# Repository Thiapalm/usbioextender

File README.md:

# USB to IO Extender Board

<p align=center>

</p>

This is a hobby development board conceived for usage in my home lab. The board can be used as USB to serial adapter with no need to install any driver on the PC. It can be used as USB to I2C adapter and also USB to GPIO port extender. For the two later options, some code development may be necessary.  

The board has 4 extra GPIO ports that can be used as LED indicators (if the back jumpers are soldered). The board power is provided by the USB connector, and it can be used in 5V or 3V3 modes for serial, I2C and GPIO pins. 

## License and certification

This is an open source hardware project licensed under CERN-OHL-P. More details on [LICENSE.md](./LICENSE.md).  

This project is certified by OSHW: [Certification BR000019](https://certification.oshwa.org/br000019.html)

## Project

The PCB project was developed in Kicad 9, all necessary project files are available in this repository and can be used freely, according to License.

## Board specifications

The board is based on the [**MCP2221**](https://www.microchip.com/en-us/product/MCP2221), and [**MCP23017**](https://www.microchip.com/en-us/product/MCP23017) from Microchip.  
Board features commonly used in Embedded Systems:
- USB-C connector
- I²C serial communication
- UART serial communication
- LED indicators (UART-TX, UART-RX, I²C, USB-Config and board power ON) or 4 extra GPIOs
- 16 GPIOs (5V or 3V3)
- Board power selector (5V / 3V3)
- The GPIO pins are breadboard compatible

## Board View 

## Version Revision

V1 - Not Published  
   - Added MCP23017 GPIOs on the header  
   - Added Jumper selector on LEDs  
   - Added Output voltage selection  
   - Added MCP2221 serial on Header  
   - Added MCP2221 I2C on Header   

V2 - Current Version
   - Changed USB connector to USB-C

## Firmware

There is no specific firmware for this board, but i have a driver developed in RUST for MCP23017 for use in embedded environments, see it in [crates.io](https://crates.io/crates/mcp23017-tp).

Also, you can use the IOExtender Control Center which is a software that can be used to control the I²C communication via Windows/Linux/Mac machines [iocc software](https://github.com/Thiapalm/iocc).

## Contribution

Unless you explicitly state otherwise, any contribution intentionally submitted for inclusion in the work by you, as defined in the CERN-OHL-P license, shall be licensed as above, without any additional terms or conditions.

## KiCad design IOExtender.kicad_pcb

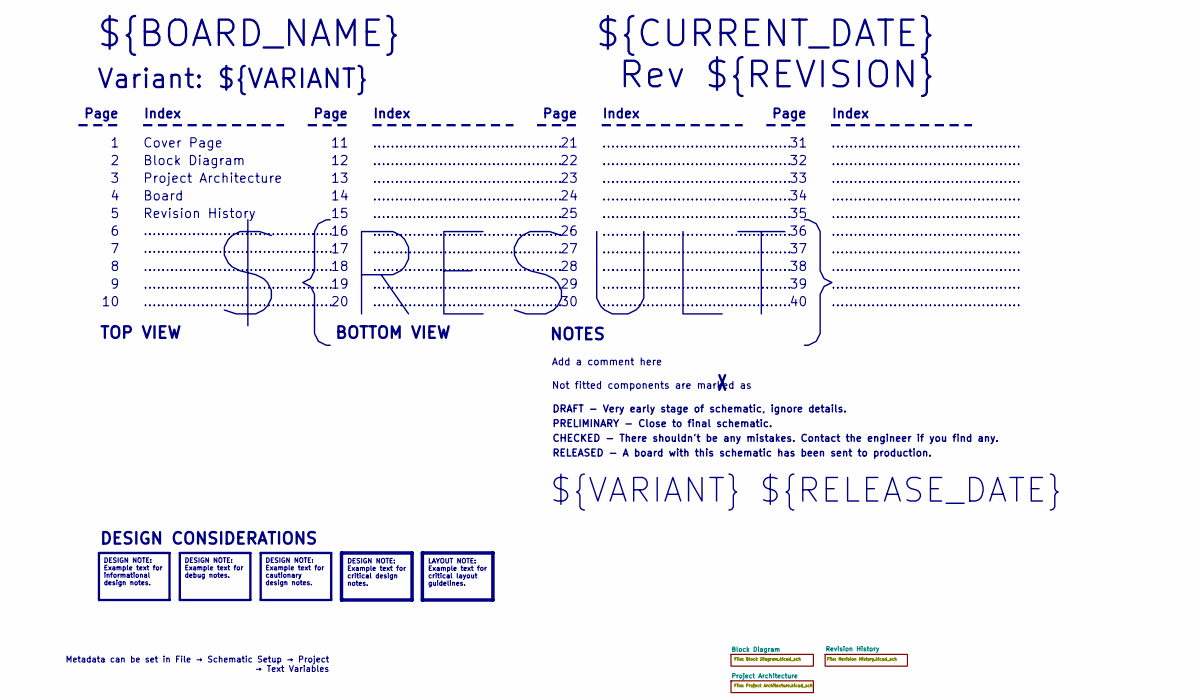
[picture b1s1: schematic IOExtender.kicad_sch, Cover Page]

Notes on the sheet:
BOTTOM VIEW
...........................................
RELEASED - A board with this schematic has been sent to production.
Page
TOP VIEW
Not fitted components are marked as
Index
PRELIMINARY - Close to final schematic.
${VARIANT} ${RELEASE_DATE}
Board
${RESULT}
${CURRENT_DATE}
Variant: ${VARIANT}
Rev ${REVISION}
${BOARD_NAME}
DRAFT - Very early stage of schematic, ignore details.
Block Diagram
Add a comment here
Cover Page
NOTES
Project Architecture
CHECKED - There shouldn't be any mistakes. Contact the engineer if you find any.
DESIGN CONSIDERATIONS
Revision History
Metadata can be set in File → Schematic Setup → Project → Text Variables
DESIGN NOTE: Example text for informational design notes.
LAYOUT NOTE: Example text for critical layout guidelines.
DESIGN NOTE: Example text for cautionary design notes.
DESIGN NOTE: Example text for debug notes.
DESIGN NOTE: Example text for critical design notes.

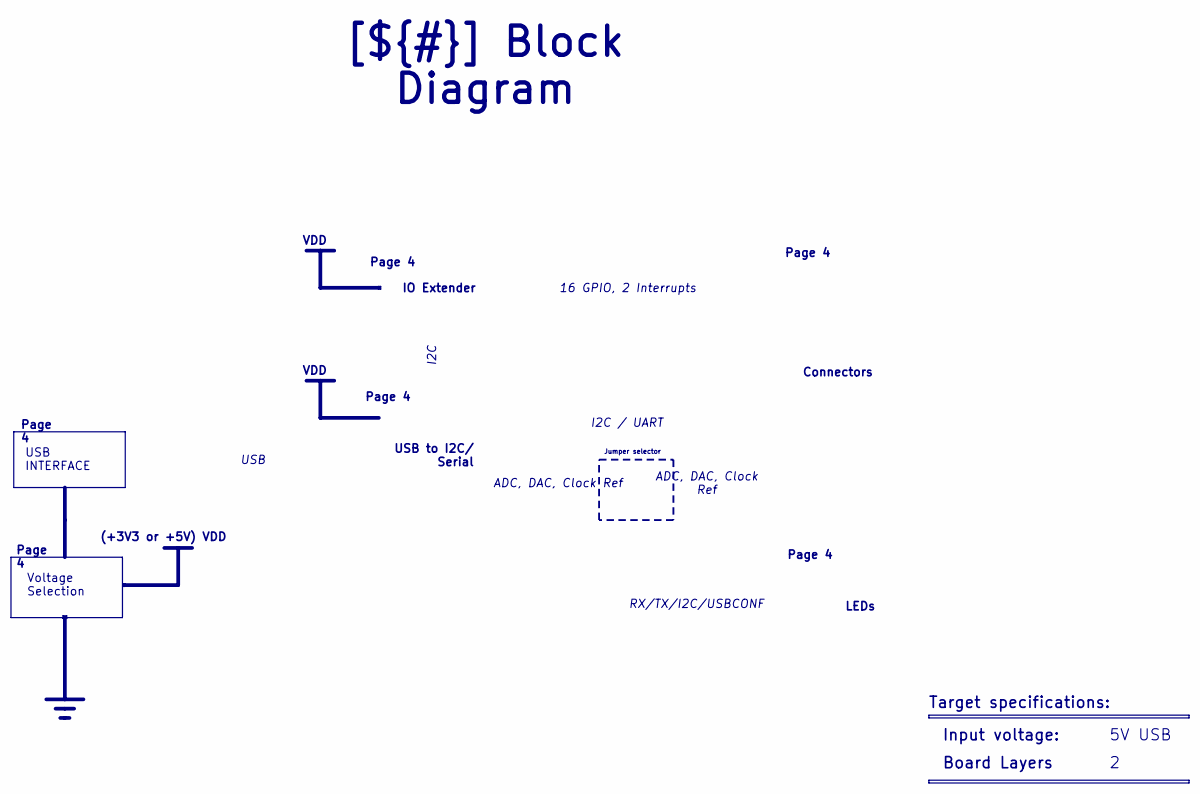
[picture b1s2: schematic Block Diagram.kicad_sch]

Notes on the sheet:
(+3V3 or +5V) VDD
VDD
Jumper selector
USB INTERFACE
Connectors
Board Layers
ADC, DAC, Clock Ref
Page 4
Input voltage:
USB
USB to I2C/ Serial
16 GPIO, 2 Interrupts
IO Extender
[${#}] ${TITLE}
Target specifications:
5V USB
I2C
RX/TX/I2C/USBCONF
I2C / UART
LEDs
Voltage Selection

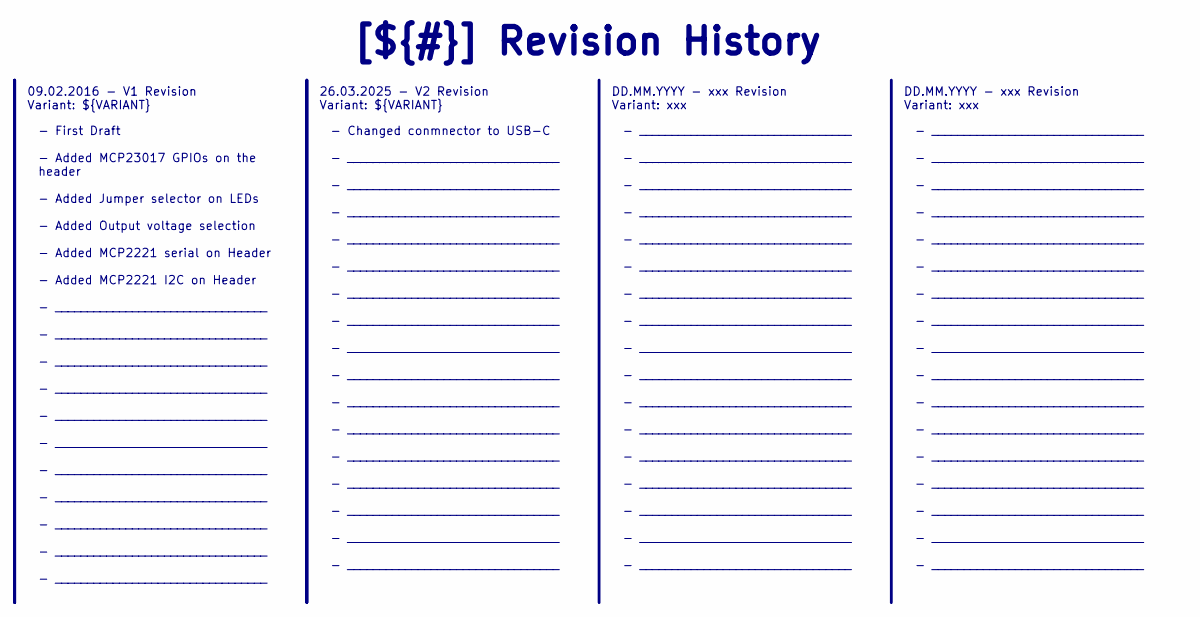
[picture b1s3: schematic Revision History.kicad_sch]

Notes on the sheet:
- _________________________________ - _________________________________ - _________________________________ - _________________________________ - _________________________________ - _________________________________ - _________________________________ - _________________________________ - _________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
26.03.2025 - V2 Revision Variant: ${VARIANT}
[${#}] ${TITLE}
DD.MM.YYYY - xxx Revision Variant: xxx
- First Draft - Added MCP23017 GPIOs on the header - Added Jumper selector on LEDs - Added Output voltage selection - Added MCP2221 serial on Header - Added MCP2221 I2C on Header - _________________________________ - _________________________________ - _________________________________ - __________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
09.02.2016 - V1 Revision Variant: ${VARIANT}
- Changed conmnector to USB-C - _________________________________ - _________________________________ - _________________________________ - _________________________________ - _________________________________ - _________________________________ - _________________________________ - _______________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

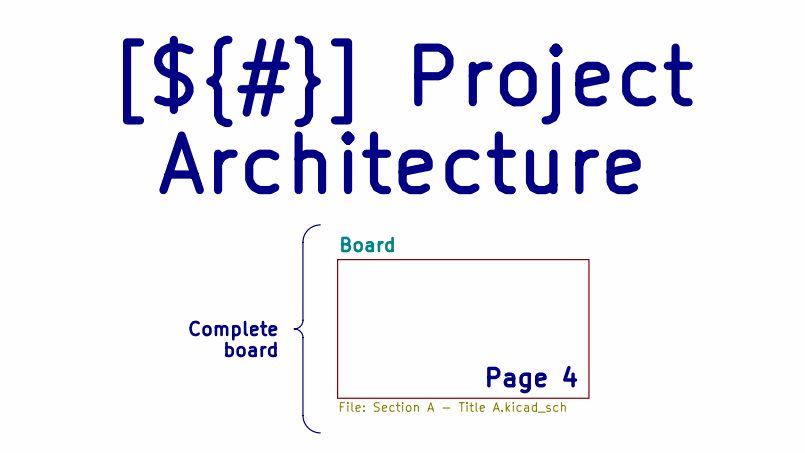
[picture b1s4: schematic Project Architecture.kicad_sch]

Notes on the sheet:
Page 4
Complete board
[${#}] ${TITLE}

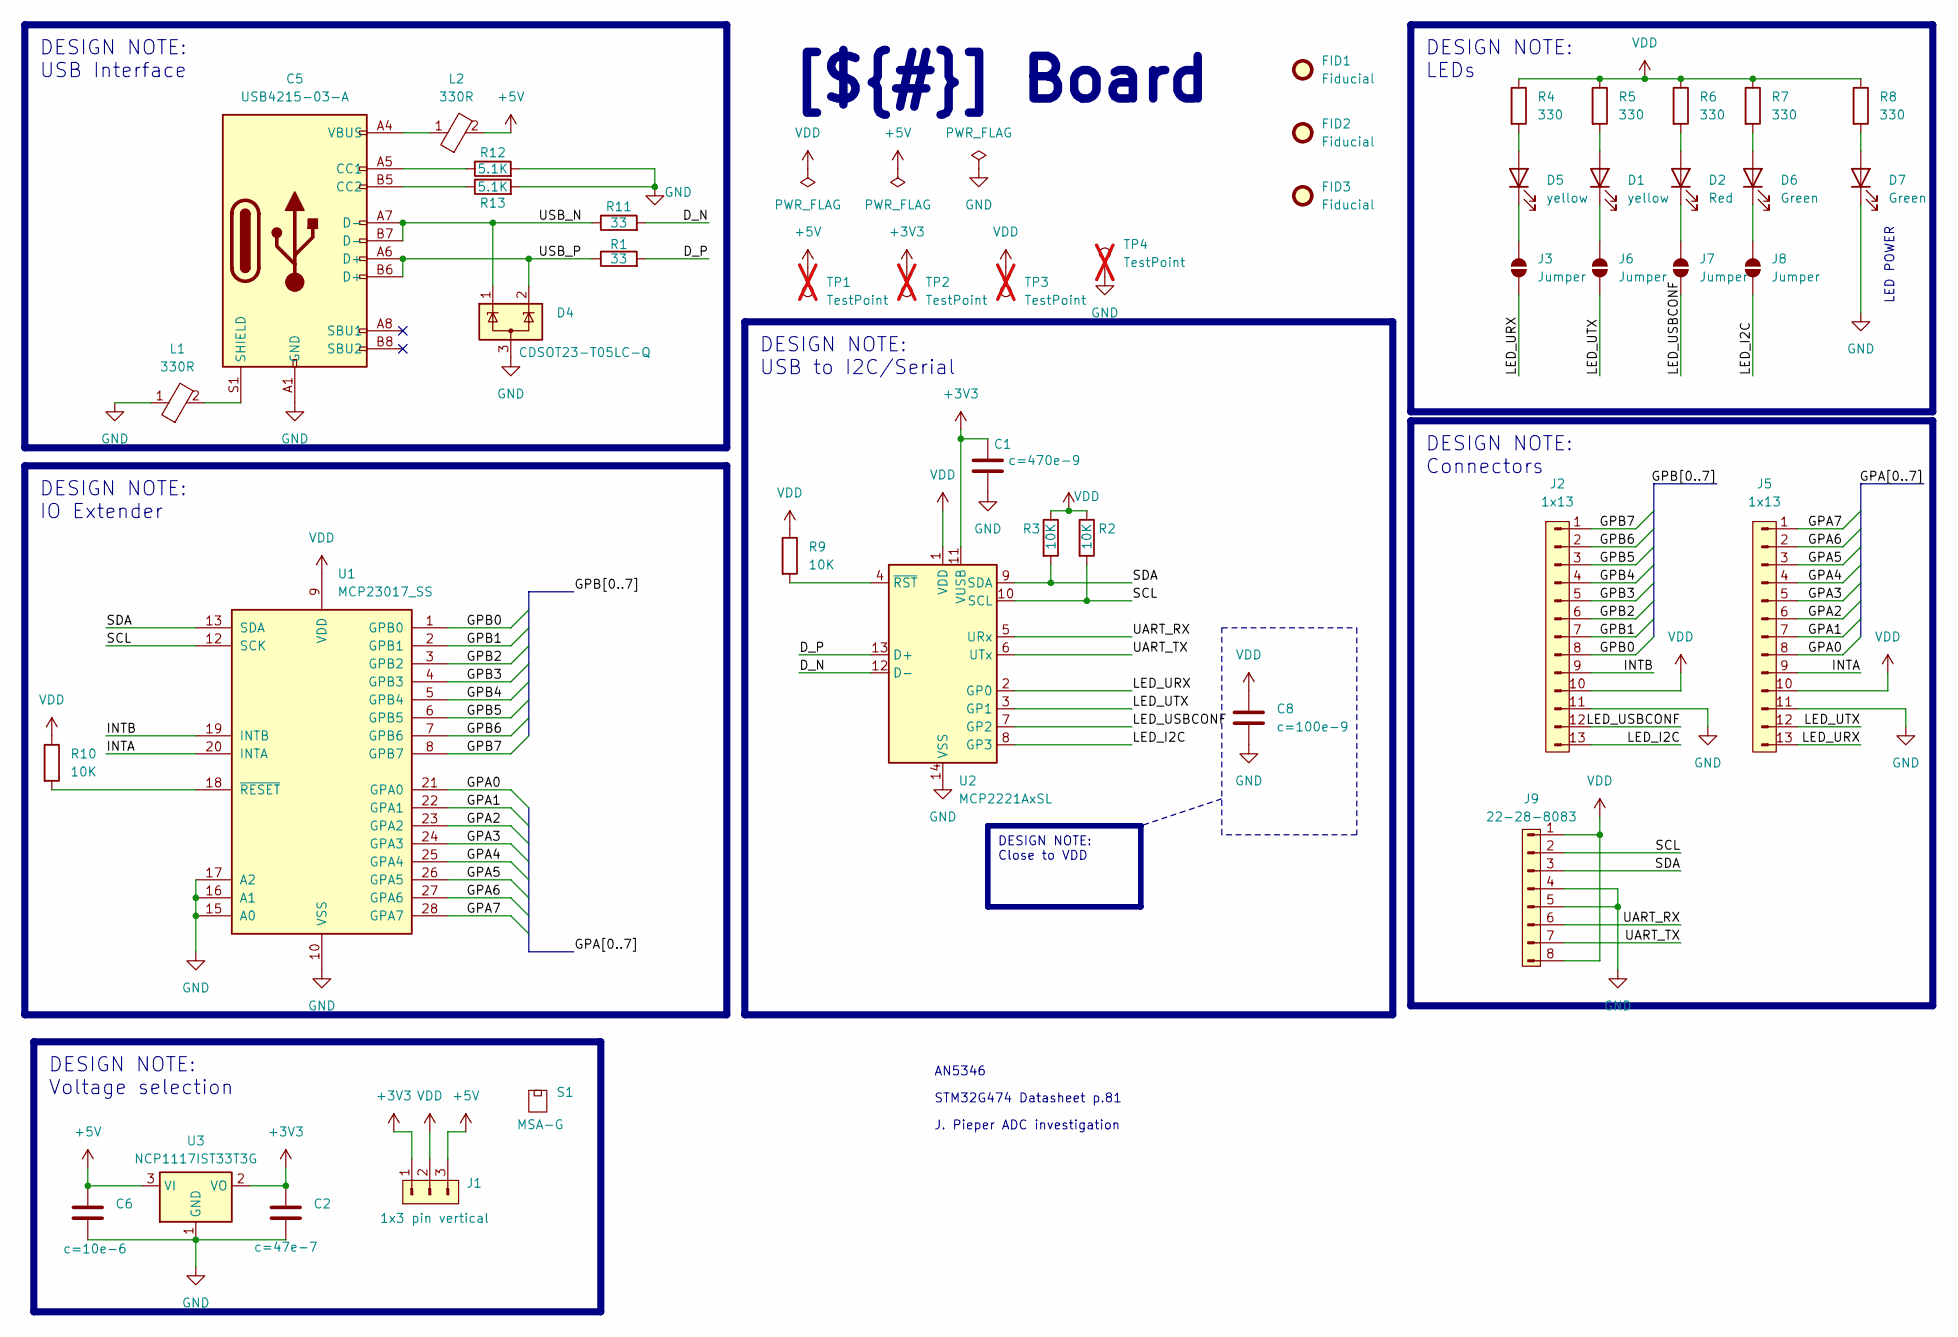
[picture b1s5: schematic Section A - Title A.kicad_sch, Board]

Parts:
C1: c=470e-9; C_0603_1608Metric_Pad1.08x0.95mm_HandSolder; Manufacturer Part Number C0603C474K3RACTU
C2: c=47e-7; C_0603_1608Metric_Pad1.08x0.95mm_HandSolder; Manufacturer Part Number GRM188R61E475KE11D
C5: USB4215-03-A; USB_C_Receptacle_GCT_USB4105-xx-A_16P_TopMnt_Horizontal; Manufacturer Part Number USB4215-03-A
C6: c=10e-6; C_0603_1608Metric_Pad1.08x0.95mm_HandSolder; Manufacturer Part Number C1608X5R1C106M080AB
C8: c=100e-9; C_0805_2012Metric_Pad1.18x1.45mm_HandSolder; Manufacturer Part Number 0805B104K500CT
D1, D5: yellow; LED_0603_1608Metric; Manufacturer Part Number LTST-C191KSKT
D2: Red; LED_0603_1608Metric; Manufacturer Part Number SM0603SRC
D4: CDSOT23-T05LC-Q; SOT-23-3; Manufacturer Part Number CDSOT23-T05LC-Q
D6, D7: Green; LED_0603_1608Metric; Manufacturer Part Number SML-LX0603GW-TR
FID1, FID2, FID3: Fiducial; Fiducial_0.5mm_Mask1.5mm
J1: 1x3 pin vertical; PinHeader_1x03_P2.54mm_Vertical; Manufacturer Part Number G800LR305018EU
J2, J5: 1x13; PinHeader_1x13_P2.54mm_Vertical; Manufacturer Part Number 61301311121
J3, J6, J7, J8: Jumper; SolderJumper-2_P1.3mm_Open_TrianglePad1.0x1.5mm
J9: 22-28-8083; PinHeader_1x08_P2.54mm_Horizontal; Manufacturer Part Number 22-28-8083
L1, L2: 330R; R_0805_2012Metric_Pad1.20x1.40mm_HandSolder; Manufacturer Part Number MPZ2012S331AT000
R1, R11: 33; R_0603_1608Metric_Pad0.98x0.95mm_HandSolder; Manufacturer Part Number CRCW060333R0FKEA
R2, R3, R9, R10: 10K; R_0603_1608Metric_Pad0.98x0.95mm_HandSolder; Manufacturer Part Number CRCW060333R0FKEA
R4, R5, R6, R7, R8: 330; R_0603_1608Metric_Pad0.98x0.95mm_HandSolder; Manufacturer Part Number ERJ-3GEYJ331V
R12, R13: 5.1K; R_0603_1608Metric_Pad0.98x0.95mm_HandSolder; Manufacturer Part Number CRCW06035K10FKEC
S1: MSA-G; Manufacturer Part Number MSA-G
TP1, TP2, TP3, TP4: TestPoint; TestPoint_PTH_1mm_2mm; not fitted
U1: MCP23017_SS; SSOP-28_5.3x10.2mm_P0.65mm; Manufacturer Part Number MCP23017_SS
U2: MCP2221AxSL; SOIC-14_3.9x8.7mm_P1.27mm; Manufacturer Part Number MCP2221AxSL
U3: NCP1117IST33T3G; SOT-223-3_TabPin2; Manufacturer Part Number NCP1117IST33T3G

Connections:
+3V3: C1.2, C2.2, J1.1, TP2.1, U2.11 (VUSB), U3.2 (VO)
+5V: C6.2, J1.3, L2.2, TP1.1, U3.3 (VI)
/Project Architecture/Board/D_N: R11.2, U2.12 (D-)
/Project Architecture/Board/D_P: R1.2, U2.13 (D+)
/Project Architecture/Board/GPA0: J5.8, U1.21 (GPA0)
/Project Architecture/Board/GPA1: J5.7, U1.22 (GPA1)
/Project Architecture/Board/GPA2: J5.6, U1.23 (GPA2)
/Project Architecture/Board/GPA3: J5.5, U1.24 (GPA3)
/Project Architecture/Board/GPA4: J5.4, U1.25 (GPA4)
/Project Architecture/Board/GPA5: J5.3, U1.26 (GPA5)
/Project Architecture/Board/GPA6: J5.2, U1.27 (GPA6)
/Project Architecture/Board/GPA7: J5.1, U1.28 (GPA7)
/Project Architecture/Board/GPB0: J2.8, U1.1 (GPB0)
/Project Architecture/Board/GPB1: J2.7, U1.2 (GPB1)
/Project Architecture/Board/GPB2: J2.6, U1.3 (GPB2)
/Project Architecture/Board/GPB3: J2.5, U1.4 (GPB3)
/Project Architecture/Board/GPB4: J2.4, U1.5 (GPB4)
/Project Architecture/Board/GPB5: J2.3, U1.6 (GPB5)
/Project Architecture/Board/GPB6: J2.2, U1.7 (GPB6)
/Project Architecture/Board/GPB7: J2.1, U1.8 (GPB7)
/Project Architecture/Board/INTA: J5.9, U1.20 (INTA)
/Project Architecture/Board/INTB: J2.9, U1.19 (INTB)
/Project Architecture/Board/LED_I2C: J2.13, J8.1 (A), U2.8 (GP3)
/Project Architecture/Board/LED_URX: J3.1 (A), J5.13, U2.2 (GP0)
/Project Architecture/Board/LED_USBCONF: J2.12, J7.1 (A), U2.7 (GP2)
/Project Architecture/Board/LED_UTX: J5.12, J6.1 (A), U2.3 (GP1)
/Project Architecture/Board/SCL: J9.2, R2.2, U1.12 (SCK), U2.10 (SCL)
/Project Architecture/Board/SDA: J9.3, R3.2, U1.13 (SDA), U2.9 (SDA)
/Project Architecture/Board/UART_RX: J9.6, U2.5 (URx)
/Project Architecture/Board/UART_TX: J9.7, U2.6 (UTx)
/Project Architecture/Board/USB_N: C5.A7 (D-), C5.B7 (D-), D4.1 (K), R11.1
/Project Architecture/Board/USB_P: C5.A6 (D+), C5.B6 (D+), D4.2 (K), R1.1
GND: C1.1, C2.1, C5.A1 (GND), C5.A12 (GND), C5.B1 (GND), C5.B12 (GND), C6.1, C8.1, D4.3 (A), D7.1 (K), J2.11, J5.11, J9.4, J9.5, L1.1, R12.2, R13.2, TP4.1, U1.10 (VSS), U1.15 (A0), U1.16 (A1), U1.17 (A2), U2.14 (VSS), U3.1 (GND)
unnamed: C5.A5 (CC1), R12.1
unnamed: C5.B5 (CC2), R13.1
unnamed: C5.S1 (SHIELD), L1.2
unnamed: C5.A4 (VBUS), C5.A9 (VBUS), C5.B4 (VBUS), C5.B9 (VBUS), L2.1
unnamed: D1.2 (A), R5.2
unnamed: D1.1 (K), J6.2 (B)
unnamed: D2.2 (A), R6.2
unnamed: D2.1 (K), J7.2 (B)
unnamed: D5.2 (A), R4.2
unnamed: D5.1 (K), J3.2 (B)
unnamed: D6.2 (A), R7.2
unnamed: D6.1 (K), J8.2 (B)
unnamed: D7.2 (A), R8.2
unnamed: R10.2, U1.18 (~RESET)
unnamed: R9.2, U2.4 (~RST)
VDD: C8.2, J1.2, J2.10, J5.10, J9.1, J9.8, R2.1, R3.1, R4.1, R5.1, R6.1, R7.1, R8.1, R9.1, R10.1, TP3.1, U1.9 (VDD), U2.1 (VDD)

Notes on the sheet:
LED POWER
J. Pieper ADC investigation
STM32G474 Datasheet p.81
AN5346
DESIGN NOTE: USB to I2C/Serial
DESIGN NOTE: Voltage selection
DESIGN NOTE: USB Interface
DESIGN NOTE: LEDs
[${#}] ${TITLE}
DESIGN NOTE: Close to VDD
DESIGN NOTE: Connectors
DESIGN NOTE: IO Extender

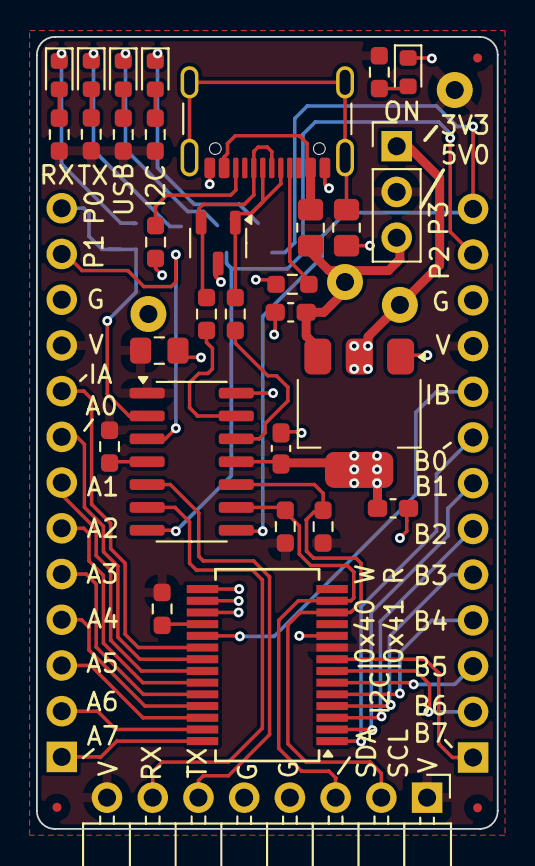
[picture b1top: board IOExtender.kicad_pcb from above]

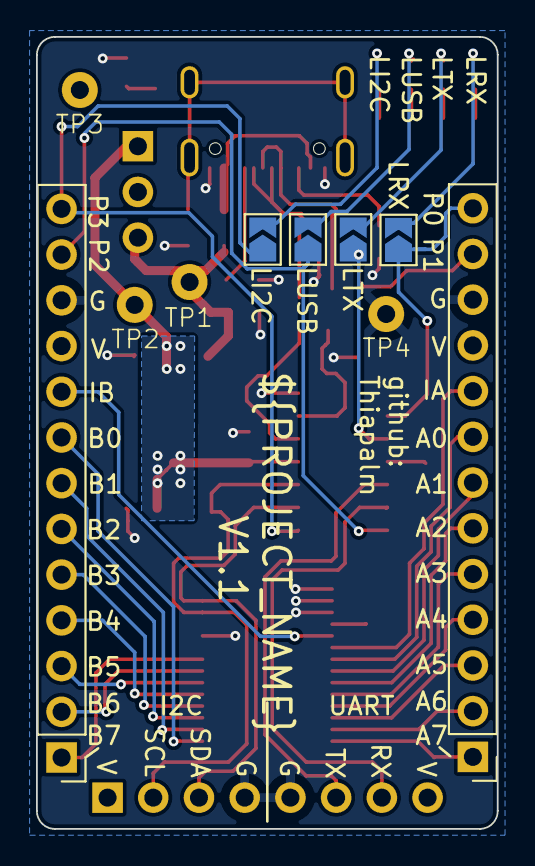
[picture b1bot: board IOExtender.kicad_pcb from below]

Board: 2 copper layers, 25.6 x 44.0 mm, 44 parts (10 on the bottom side), 49 nets.

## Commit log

2025-03-26 Finished board design, outputs generated
2025-03-26 Removed unnecessary files
2025-03-26 Updated Fabrication Files
2025-03-26 Removed power sequencing file
2025-03-29 Added certification information on README.md
2025-06-03 Update README.md
    Added iocc software link

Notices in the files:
README.md:
License: CERN OHL P
